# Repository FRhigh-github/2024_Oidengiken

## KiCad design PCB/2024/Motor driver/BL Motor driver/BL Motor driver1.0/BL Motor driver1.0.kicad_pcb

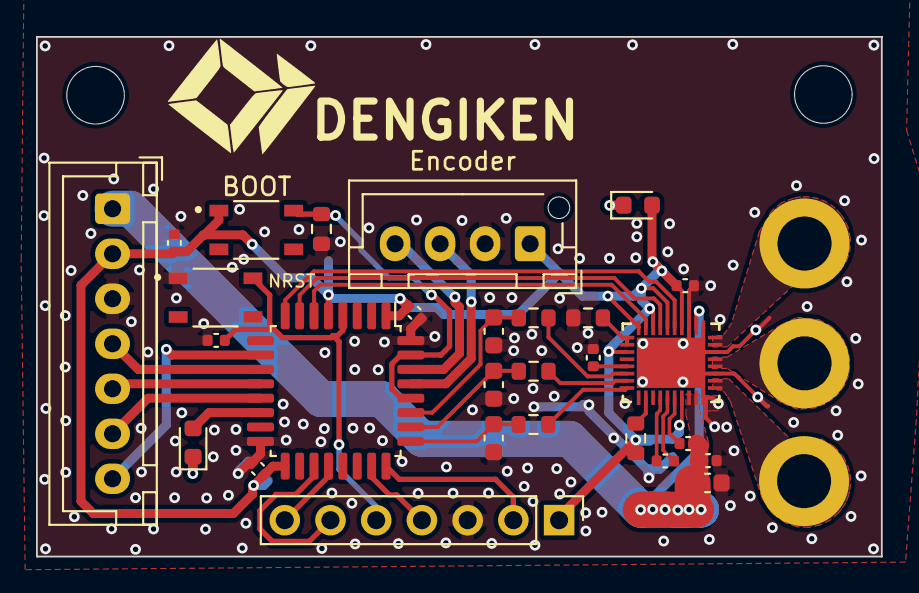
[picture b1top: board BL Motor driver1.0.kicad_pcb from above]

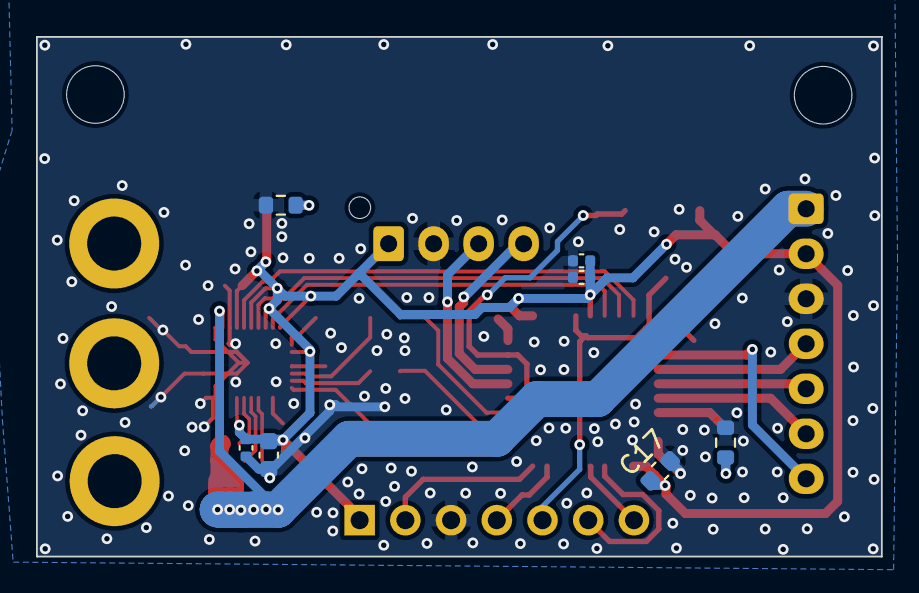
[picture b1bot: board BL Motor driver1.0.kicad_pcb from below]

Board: 2 copper layers, 46.9 x 28.9 mm, 38 parts (7 on the bottom side), 36 nets.

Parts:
BOOT: BOOT; SW_SKRPABE010
C1, C3, C6, C10, C12, C14, C16, C18: 0.1u; C_0402_1005Metric
C2, C4: 10u; C_0603_1608Metric
C5, C15: 1u; C_0402_1005Metric
C7, C8, C9: 22p; C_0603_1608Metric
C11: 2.2u; C_0402_1005Metric
C13: 0.01u; C_0402_1005Metric
C17: 4.7uf; C_0603_1608Metric
D1: UI_LED; LED_0603_1608Metric
D2: 3.3V_LED; LED_0603_1608Metric
Encoder: Encoder; JST_XH_B4B-XH-AM_1x04_P2.50mm_Vertical
J1: U; BLDC
J3: Main; JST_XH_B7B-XH-A_1x07_P2.50mm_Vertical
J4: V; BLDC
J6: PC; PinHeader_1x07_P2.54mm_Vertical
NRST: NRST; SW_SKRPABE010
R1, R2, R3: 330; R_0603_1608Metric
R4: 47k; R_0603_1608Metric
R5: 5.1k; R_0603_1608Metric
R6, R7, R8: 10k; R_0603_1608Metric
U1: DRV8317HREER
U2: STM32F303K8Tx; LQFP-32_7x7mm_P0.8mm
W: W; BLDC

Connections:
AGND: C1.2, C2.2, C3.2, C4.2, C7.2, C8.2, C9.2, C10.2, C11.2, C12.2, C13.2, C14.2, C15.2, C16.2, C17.2, C18.2, Encoder.2, J3.3, J6.3, NRST.1, R4.2, R6.2, R7.2, R8.2, U1.10 (PGND), U1.13 (PGND), U1.16 (PGND), U1.19 (PGND), U1.21 (AGND), U1.37 (EPAD), U2.16 (VSS), U2.32 (VSS)
AVDD: BOOT.1, C1.1, C2.1, C11.1, C12.1, C13.1, C14.1, C15.1, C16.1, C17.1, D2.2 (A), Encoder.1, J3.2, J6.1, R5.1, U1.7 (VIN_AVDD), U1.22 (AVDD), U1.24 (INLA), U1.26 (INLB), U1.28 (INLC), U1.31 (MODE), U2.1 (VDD), U2.5 (VDDA), U2.17 (VDD)
BOOT: BOOT.2, R6.1, U2.28 (PB5), U2.31 (BOOT0)
CP: C5.2, U1.6 (CP)
CPH: C6.1, U1.5 (CPH)
CPL: C6.2, U1.4 (CPL)
CSAREF: C10.1, U1.33 (CSAREF)
GAIN: R4.1, U1.29 (GAIN), U1.30 (SLEW)
I2C_SCL: Encoder.3, U2.29 (PB6)
I2C_SDA: Encoder.4, U2.30 (PB7)
NRST: C18.1, J6.5, NRST.2, U2.4 (NRST)
unnamed: D1.1 (K), R7.1
unnamed: D2.1 (K), R8.1
PWMU: U1.23 (INHA), U2.8 (PA2)
PWMV: U1.25 (INHB), U2.7 (PA1)
PWMW: U1.27 (INHC), U2.6 (PA0)
SOA: R1.2, U1.36 (SOA)
SOB: R2.2, U1.35 (SOB)
SOC: R3.2, U1.34 (SOC)
SOU: C7.1, R1.1, U2.25 (PA15)
SOV: C8.1, R2.1, U2.26 (PB3)
SOW: C9.1, R3.1, U2.27 (PB4)
SPI_CS: J3.7, U2.10 (PA4)
SPI_MISO: J3.5, U2.12 (PA6)
SPI_MOSI: J3.6, U2.13 (PA7)
SPI_SCK: J3.4, U2.11 (PA5)
SWCLK: J6.2, U2.24 (PA14)
SWDIO: J6.4, U2.23 (PA13)
U: J1.1, U1.11 (OUTA), U1.12 (OUTA)
UI_LED: D1.2 (A), U2.14 (PB0)
USART1_RX: J6.7, U2.20 (PA10)
USART1_TX: J6.6, U2.19 (PA9)
V: J4.1, U1.14 (OUTB), U1.15 (OUTB)
VM: C3.1, C4.1, C5.1, J3.1, U1.8 (VM), U1.9 (VM), U1.20 (VM)
W: U1.17 (OUTC), U1.18 (OUTC), W.1
nFAULT: R5.2, U1.2 (NFAULT)

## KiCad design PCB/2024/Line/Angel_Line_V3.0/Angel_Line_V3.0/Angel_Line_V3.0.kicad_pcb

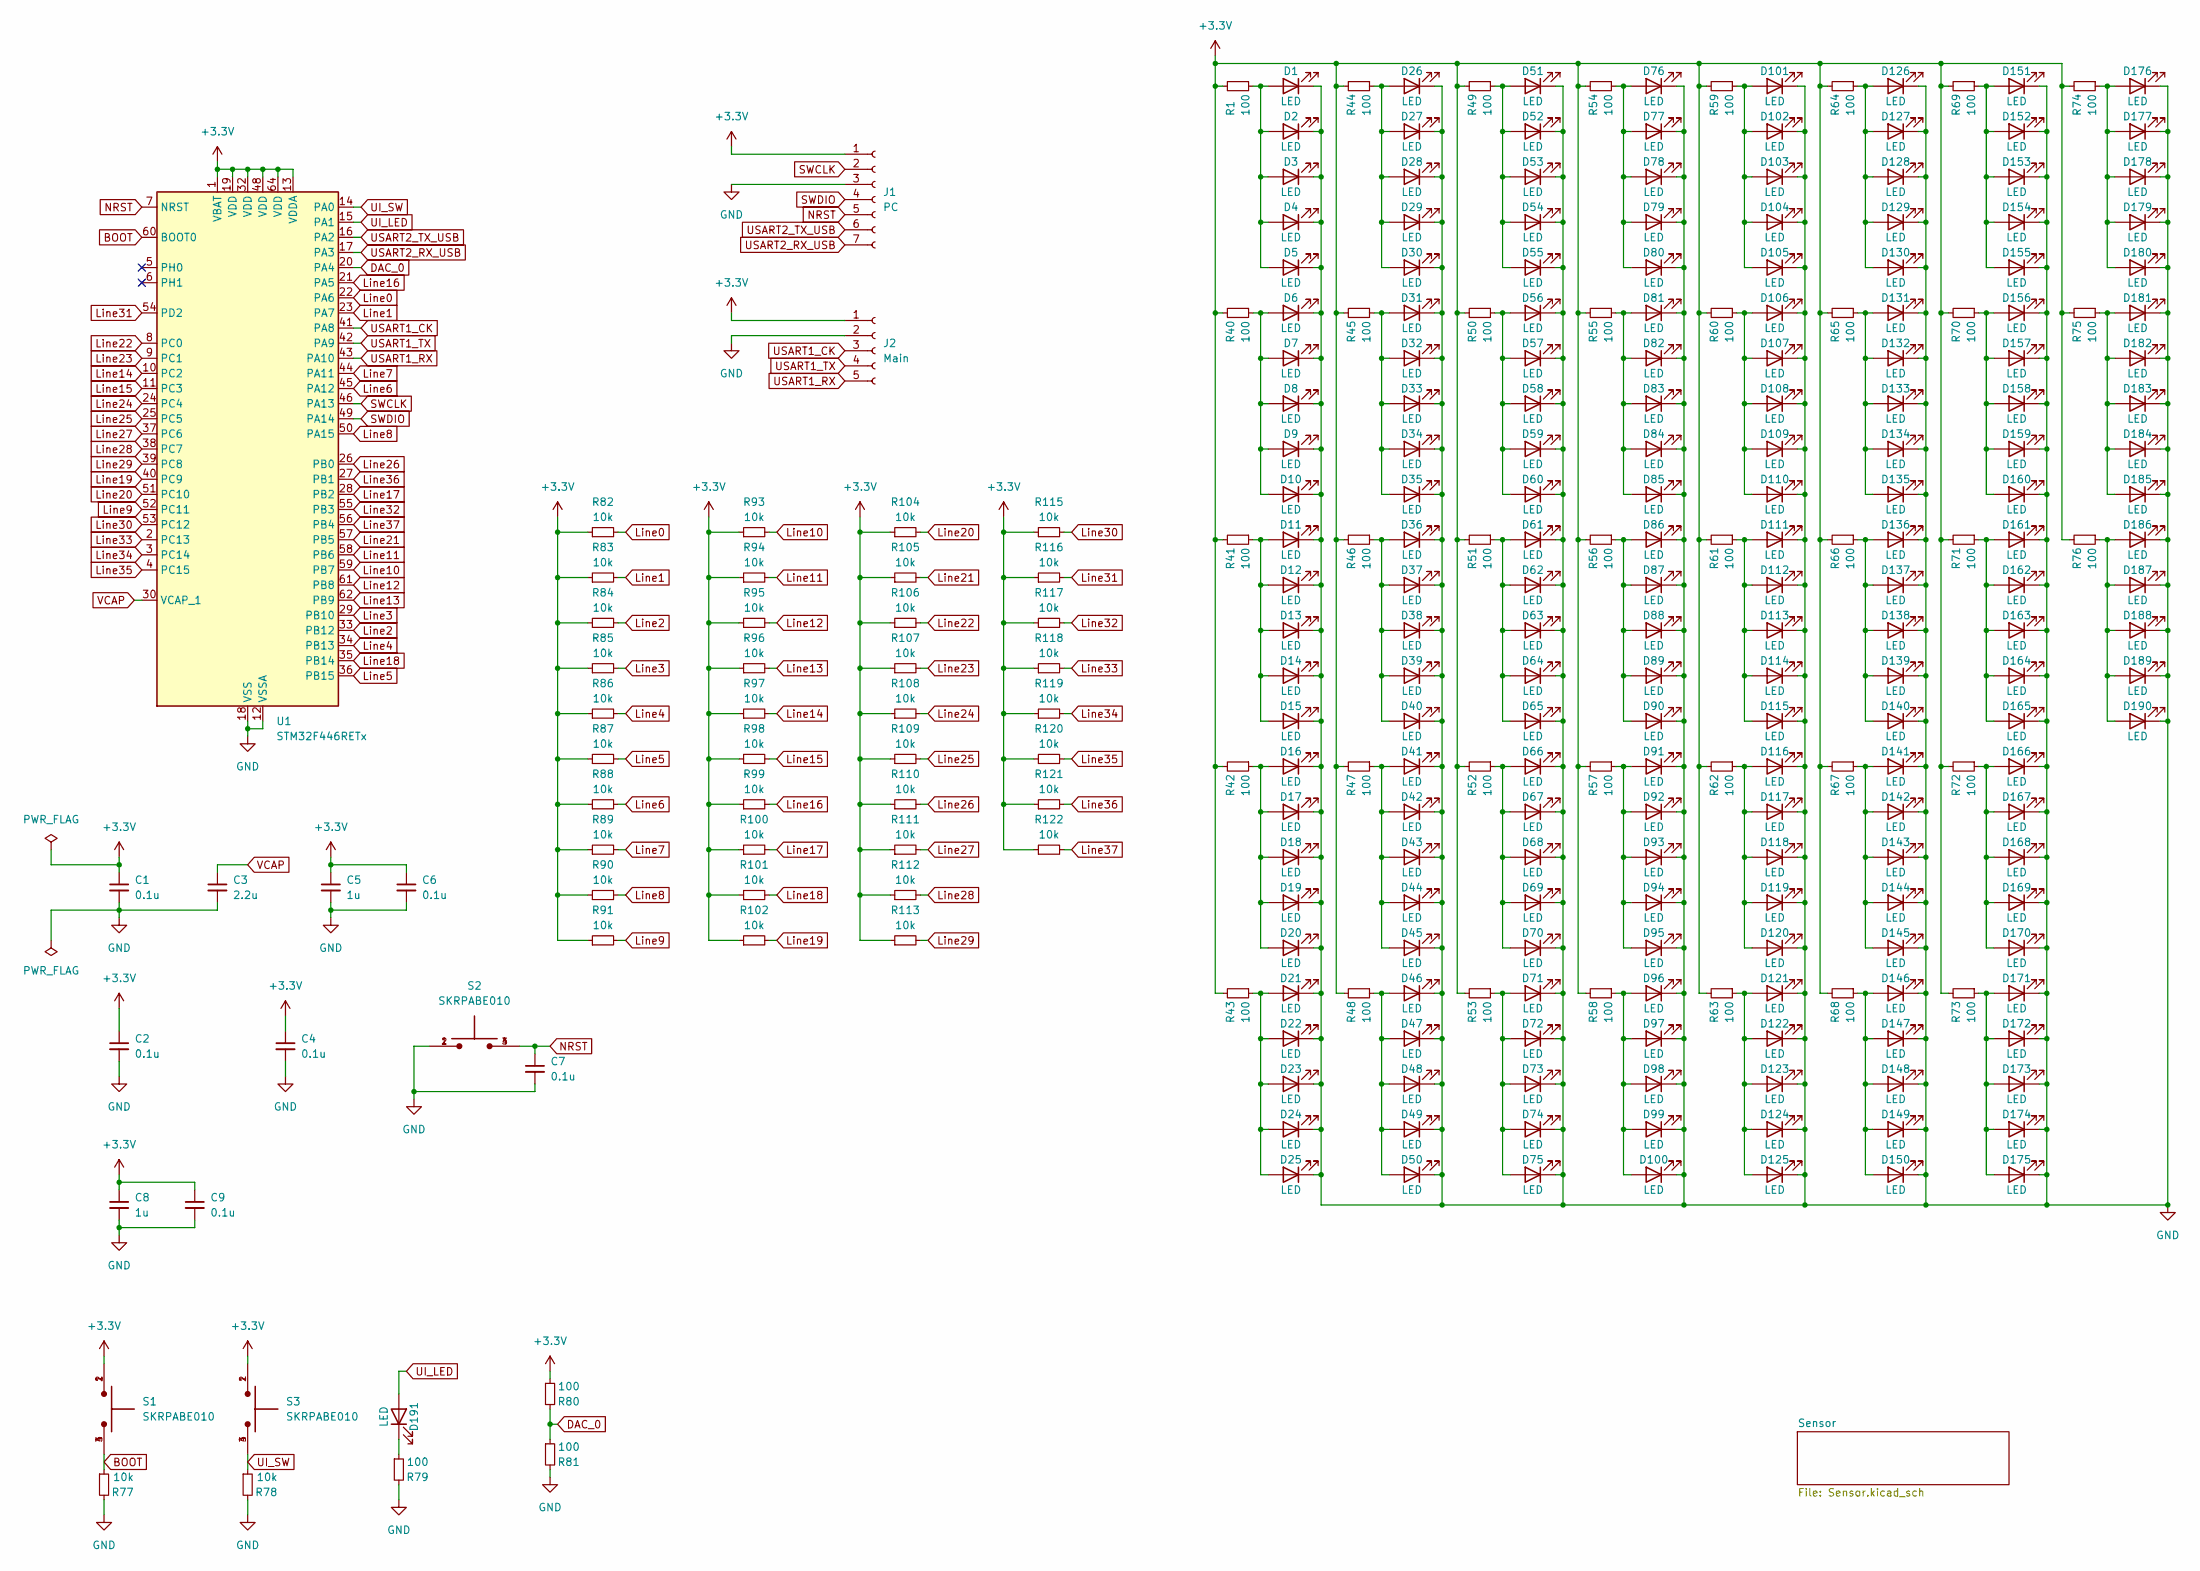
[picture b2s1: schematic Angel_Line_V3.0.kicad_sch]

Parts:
C1, C2, C4, C6, C7, C9: 0.1u; C_0402_1005Metric
C3: 2.2u; C_0603_1608Metric
C5, C8: 1u; C_0402_1005Metric
D1, D2, D3, D4, D5, D6, D7, D8, D9, D10, D11, D12, D13, D14, D15, D16, D17, D18, D19, D20, D21, D22, D23, D24, D25, D26, D27, D28, D29, D30, D31, D32, D33, D34, D35, D36, D37, D38, D39, D40, D41, D42, D43, D44, D45, D46, D47, D48, D49, D50, D51, D52, D53, D54, D55, D56, D57, D58, D59, D60, D61, D62, D63, D64, D65, D66, D67, D68, D69, D70, D71, D72, D73, D74, D75, D76, D77, D78, D79, D80, D81, D82, D83, D84, D85, D86, D87, D88, D89, D90, D91, D92, D93, D94, D95, D96, D97, D98, D99, D100, D101, D102, D103, D104, D105, D106, D107, D108, D109, D110, D111, D112, D113, D114, D115, D116, D117, D118, D119, D120, D121, D122, D123, D124, D125, D126, D127, D128, D129, D130, D131, D132, D133, D134, D135, D136, D137, D138, D139, D140, D141, D142, D143, D144, D145, D146, D147, D148, D149, D150, D151, D152, D153, D154, D155, D156, D157, D158, D159, D160, D161, D162, D163, D164, D165, D166, D167, D168, D169, D170, D171, D172, D173, D174, D175, D176, D177, D178, D179, D180, D181, D182, D183, D184, D185, D186, D187, D188, D189, D190, D191: LED; LED_0603_1608Metric
J1: PC; JST_XH_B7B-XH-A_1x07_P2.50mm_Vertical
J2: Main; JST_XH_B5B-XH-A_1x05_P2.50mm_Vertical
R1, R40, R41, R42, R43, R44, R45, R46, R47, R48, R49, R50, R51, R52, R53, R54, R55, R56, R57, R58, R59, R60, R61, R62, R63, R64, R65, R66, R67, R68, R69, R70, R71, R72, R73, R74, R75, R76, R79, R80, R81: 100; R_0603_1608Metric
R77, R78, R82, R83, R84, R85, R86, R87, R88, R89, R90, R91, R93, R94, R95, R96, R97, R98, R99, R100, R101, R102, R104, R105, R106, R107, R108, R109, R110, R111, R112, R113, R115, R116, R117, R118, R119, R120, R121, R122: 10k; R_0603_1608Metric
S1, S2, S3: SKRPABE010; SW_SKRPABE010
U1: STM32F446RETx; LQFP-64_10x10mm_P0.5mm

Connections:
+3.3V: C1.1, C2.1, C4.1, C5.1, C6.1, C8.1, C9.1, J1.1, J2.1, R1.2, R40.2, R41.2, R42.2, R43.2, R44.2, R45.2, R46.2, R47.2, R48.2, R49.2, R50.2, R51.2, R52.2, R53.2, R54.2, R55.2, R56.2, R57.2, R58.2, R59.2, R60.2, R61.2, R62.2, R63.2, R64.2, R65.2, R66.2, R67.2, R68.2, R69.2, R70.2, R71.2, R72.2, R73.2, R74.2, R75.2, R76.2, R80.1, R82.1, R83.1, R84.1, R85.1, R86.1, R87.1, R88.1, R89.1, R90.1, R91.1, R93.1, R94.1, R95.1, R96.1, R97.1, R98.1, R99.1, R100.1, R101.1, R102.1, R104.1, R105.1, R106.1, R107.1, R108.1, R109.1, R110.1, R111.1, R112.1, R113.1, R115.1, R116.1, R117.1, R118.1, R119.1, R120.1, R121.1, R122.1, S1.1, S1.2, S3.1, S3.2, U1.1 (VBAT), U1.13 (VDDA), U1.19 (VDD), U1.32 (VDD), U1.48 (VDD), U1.64 (VDD); also elsewhere on the board
BOOT: R77.1, S1.3, S1.4, U1.60 (BOOT0)
DAC_0: R80.2, R81.1, U1.20 (PA4); also elsewhere on the board
GND: C1.2, C2.2, C3.2, C4.2, C5.2, C6.2, C7.2, C8.2, C9.2, D1.1 (K), D2.1 (K), D3.1 (K), D4.1 (K), D5.1 (K), D6.1 (K), D7.1 (K), D8.1 (K), D9.1 (K), D10.1 (K), D11.1 (K), D12.1 (K), D13.1 (K), D14.1 (K), D15.1 (K), D16.1 (K), D17.1 (K), D18.1 (K), D19.1 (K), D20.1 (K), D21.1 (K), D22.1 (K), D23.1 (K), D24.1 (K), D25.1 (K), D26.1 (K), D27.1 (K), D28.1 (K), D29.1 (K), D30.1 (K), D31.1 (K), D32.1 (K), D33.1 (K), D34.1 (K), D35.1 (K), D36.1 (K), D37.1 (K), D38.1 (K), D39.1 (K), D40.1 (K), D41.1 (K), D42.1 (K), D43.1 (K), D44.1 (K), D45.1 (K), D46.1 (K), D47.1 (K), D48.1 (K), D49.1 (K), D50.1 (K), D51.1 (K), D52.1 (K), D53.1 (K), D54.1 (K), D55.1 (K), D56.1 (K), D57.1 (K), D58.1 (K), D59.1 (K), D60.1 (K), D61.1 (K), D62.1 (K), D63.1 (K), D64.1 (K), D65.1 (K), D66.1 (K), D67.1 (K), D68.1 (K), D69.1 (K), D70.1 (K), D71.1 (K), D72.1 (K), D73.1 (K), D74.1 (K), D75.1 (K), D76.1 (K), D77.1 (K), D78.1 (K), D79.1 (K), D80.1 (K), D81.1 (K), D82.1 (K), D83.1 (K), D84.1 (K), D85.1 (K), D86.1 (K), D87.1 (K), D88.1 (K), D89.1 (K), D90.1 (K), D91.1 (K), D92.1 (K), D93.1 (K), D94.1 (K), D95.1 (K), D96.1 (K), D97.1 (K), D98.1 (K), D99.1 (K), D100.1 (K), D101.1 (K), D102.1 (K), D103.1 (K), D104.1 (K), D105.1 (K), D106.1 (K), D107.1 (K), D108.1 (K), D109.1 (K), D110.1 (K), D111.1 (K), D112.1 (K), D113.1 (K), D114.1 (K), D115.1 (K), D116.1 (K), D117.1 (K), D118.1 (K), D119.1 (K), D120.1 (K), D121.1 (K), D122.1 (K), D123.1 (K), D124.1 (K), D125.1 (K), D126.1 (K), D127.1 (K), D128.1 (K), D129.1 (K), D130.1 (K), D131.1 (K), D132.1 (K), D133.1 (K), D134.1 (K), D135.1 (K), D136.1 (K), D137.1 (K), D138.1 (K), D139.1 (K), D140.1 (K), D141.1 (K), D142.1 (K), D143.1 (K), D144.1 (K), D145.1 (K), D146.1 (K), D147.1 (K), D148.1 (K), D149.1 (K), D150.1 (K), D151.1 (K), D152.1 (K), D153.1 (K), D154.1 (K), D155.1 (K), D156.1 (K), D157.1 (K), D158.1 (K), D159.1 (K), D160.1 (K), D161.1 (K), D162.1 (K), D163.1 (K), D164.1 (K), D165.1 (K), D166.1 (K), D167.1 (K), D168.1 (K), D169.1 (K), D170.1 (K), D171.1 (K), D172.1 (K), D173.1 (K), D174.1 (K), D175.1 (K), D176.1 (K), D177.1 (K), D178.1 (K), D179.1 (K), D180.1 (K), D181.1 (K), D182.1 (K), D183.1 (K), D184.1 (K), D185.1 (K), D186.1 (K), D187.1 (K), D188.1 (K), D189.1 (K), D190.1 (K), J1.3, J2.2, R77.2, R78.2, R79.2, R81.2, S2.1, S2.2, U1.12 (VSSA), U1.18 (VSS), U1.31 (VSS), U1.47 (VSS), U1.63 (VSS); also elsewhere on the board
Line0: R82.2, U1.22 (PA6); also elsewhere on the board
Line1: R83.2, U1.23 (PA7); also elsewhere on the board
Line2: R84.2, U1.33 (PB12); also elsewhere on the board
Line3: R85.2, U1.29 (PB10); also elsewhere on the board
Line4: R86.2, U1.34 (PB13); also elsewhere on the board
Line5: R87.2, U1.36 (PB15); also elsewhere on the board
Line6: R88.2, U1.45 (PA12); also elsewhere on the board
Line7: R89.2, U1.44 (PA11); also elsewhere on the board
Line8: R90.2, U1.50 (PA15); also elsewhere on the board
Line9: R91.2, U1.52 (PC11); also elsewhere on the board
Line10: R93.2, U1.59 (PB7); also elsewhere on the board
Line11: R94.2, U1.58 (PB6); also elsewhere on the board
Line12: R95.2, U1.61 (PB8); also elsewhere on the board
Line13: R96.2, U1.62 (PB9); also elsewhere on the board
Line14: R97.2, U1.10 (PC2); also elsewhere on the board
Line15: R98.2, U1.11 (PC3); also elsewhere on the board
Line16: R99.2, U1.21 (PA5); also elsewhere on the board
Line17: R100.2, U1.28 (PB2); also elsewhere on the board
Line18: R101.2, U1.35 (PB14); also elsewhere on the board
Line19: R102.2, U1.40 (PC9); also elsewhere on the board
Line20: R104.2, U1.51 (PC10); also elsewhere on the board
Line21: R105.2, U1.57 (PB5); also elsewhere on the board
Line22: R106.2, U1.8 (PC0); also elsewhere on the board
Line23: R107.2, U1.9 (PC1); also elsewhere on the board
Line24: R108.2, U1.24 (PC4); also elsewhere on the board
Line25: R109.2, U1.25 (PC5); also elsewhere on the board
Line26: R110.2, U1.26 (PB0); also elsewhere on the board
Line27: R111.2, U1.37 (PC6); also elsewhere on the board
Line28: R112.2, U1.38 (PC7); also elsewhere on the board
Line29: R113.2, U1.39 (PC8); also elsewhere on the board
Line30: R115.2, U1.53 (PC12); also elsewhere on the board
Line31: R116.2, U1.54 (PD2); also elsewhere on the board
Line32: R117.2, U1.55 (PB3); also elsewhere on the board
Line33: R118.2, U1.2 (PC13); also elsewhere on the board
Line34: R119.2, U1.3 (PC14); also elsewhere on the board
Line35: R120.2, U1.4 (PC15); also elsewhere on the board
Line36: R121.2, U1.27 (PB1); also elsewhere on the board
Line37: R122.2, U1.56 (PB4); also elsewhere on the board
NRST: C7.1, J1.5, S2.3, S2.4, U1.7 (NRST)
unnamed: D1.2 (A), D2.2 (A), D3.2 (A), D4.2 (A), D5.2 (A), R1.1
unnamed: D6.2 (A), D7.2 (A), D8.2 (A), D9.2 (A), D10.2 (A), R40.1
unnamed: D11.2 (A), D12.2 (A), D13.2 (A), D14.2 (A), D15.2 (A), R41.1
unnamed: D16.2 (A), D17.2 (A), D18.2 (A), D19.2 (A), D20.2 (A), R42.1
unnamed: D21.2 (A), D22.2 (A), D23.2 (A), D24.2 (A), D25.2 (A), R43.1
unnamed: D26.2 (A), D27.2 (A), D28.2 (A), D29.2 (A), D30.2 (A), R44.1
unnamed: D31.2 (A), D32.2 (A), D33.2 (A), D34.2 (A), D35.2 (A), R45.1
unnamed: D36.2 (A), D37.2 (A), D38.2 (A), D39.2 (A), D40.2 (A), R46.1
unnamed: D41.2 (A), D42.2 (A), D43.2 (A), D44.2 (A), D45.2 (A), R47.1
unnamed: D46.2 (A), D47.2 (A), D48.2 (A), D49.2 (A), D50.2 (A), R48.1
unnamed: D51.2 (A), D52.2 (A), D53.2 (A), D54.2 (A), D55.2 (A), R49.1
unnamed: D56.2 (A), D57.2 (A), D58.2 (A), D59.2 (A), D60.2 (A), R50.1
unnamed: D61.2 (A), D62.2 (A), D63.2 (A), D64.2 (A), D65.2 (A), R51.1
unnamed: D66.2 (A), D67.2 (A), D68.2 (A), D69.2 (A), D70.2 (A), R52.1
unnamed: D71.2 (A), D72.2 (A), D73.2 (A), D74.2 (A), D75.2 (A), R53.1
unnamed: D76.2 (A), D77.2 (A), D78.2 (A), D79.2 (A), D80.2 (A), R54.1
unnamed: D81.2 (A), D82.2 (A), D83.2 (A), D84.2 (A), D85.2 (A), R55.1
unnamed: D86.2 (A), D87.2 (A), D88.2 (A), D89.2 (A), D90.2 (A), R56.1
unnamed: D91.2 (A), D92.2 (A), D93.2 (A), D94.2 (A), D95.2 (A), R57.1
unnamed: D96.2 (A), D97.2 (A), D98.2 (A), D99.2 (A), D100.2 (A), R58.1
unnamed: D101.2 (A), D102.2 (A), D103.2 (A), D104.2 (A), D105.2 (A), R59.1
unnamed: D106.2 (A), D107.2 (A), D108.2 (A), D109.2 (A), D110.2 (A), R60.1
unnamed: D111.2 (A), D112.2 (A), D113.2 (A), D114.2 (A), D115.2 (A), R61.1
unnamed: D116.2 (A), D117.2 (A), D118.2 (A), D119.2 (A), D120.2 (A), R62.1
unnamed: D121.2 (A), D122.2 (A), D123.2 (A), D124.2 (A), D125.2 (A), R63.1
unnamed: D126.2 (A), D127.2 (A), D128.2 (A), D129.2 (A), D130.2 (A), R64.1
unnamed: D131.2 (A), D132.2 (A), D133.2 (A), D134.2 (A), D135.2 (A), R65.1
unnamed: D136.2 (A), D137.2 (A), D138.2 (A), D139.2 (A), D140.2 (A), R66.1
unnamed: D141.2 (A), D142.2 (A), D143.2 (A), D144.2 (A), D145.2 (A), R67.1
unnamed: D146.2 (A), D147.2 (A), D148.2 (A), D149.2 (A), D150.2 (A), R68.1
unnamed: D151.2 (A), D152.2 (A), D153.2 (A), D154.2 (A), D155.2 (A), R69.1
unnamed: D156.2 (A), D157.2 (A), D158.2 (A), D159.2 (A), D160.2 (A), R70.1
unnamed: D161.2 (A), D162.2 (A), D163.2 (A), D164.2 (A), D165.2 (A), R71.1
unnamed: D166.2 (A), D167.2 (A), D168.2 (A), D169.2 (A), D170.2 (A), R72.1
unnamed: D171.2 (A), D172.2 (A), D173.2 (A), D174.2 (A), D175.2 (A), R73.1
unnamed: D176.2 (A), D177.2 (A), D178.2 (A), D179.2 (A), D180.2 (A), R74.1
unnamed: D181.2 (A), D182.2 (A), D183.2 (A), D184.2 (A), D185.2 (A), R75.1
unnamed: D186.2 (A), D187.2 (A), D188.2 (A), D189.2 (A), D190.2 (A), R76.1
unnamed: D191.1 (K), R79.1
SWCLK: J1.2, U1.46 (PA13)
SWDIO: J1.4, U1.49 (PA14)
UI_LED: D191.2 (A), U1.15 (PA1)
UI_SW: R78.1, S3.3, S3.4, U1.14 (PA0)
USART1_CK: J2.3, U1.41 (PA8)
USART1_RX: J2.5, U1.43 (PA10)
USART1_TX: J2.4, U1.42 (PA9)
USART2_RX_USB: J1.7, U1.17 (PA3)
USART2_TX_USB: J1.6, U1.16 (PA2)
VCAP: C3.1, U1.30 (VCAP_1)

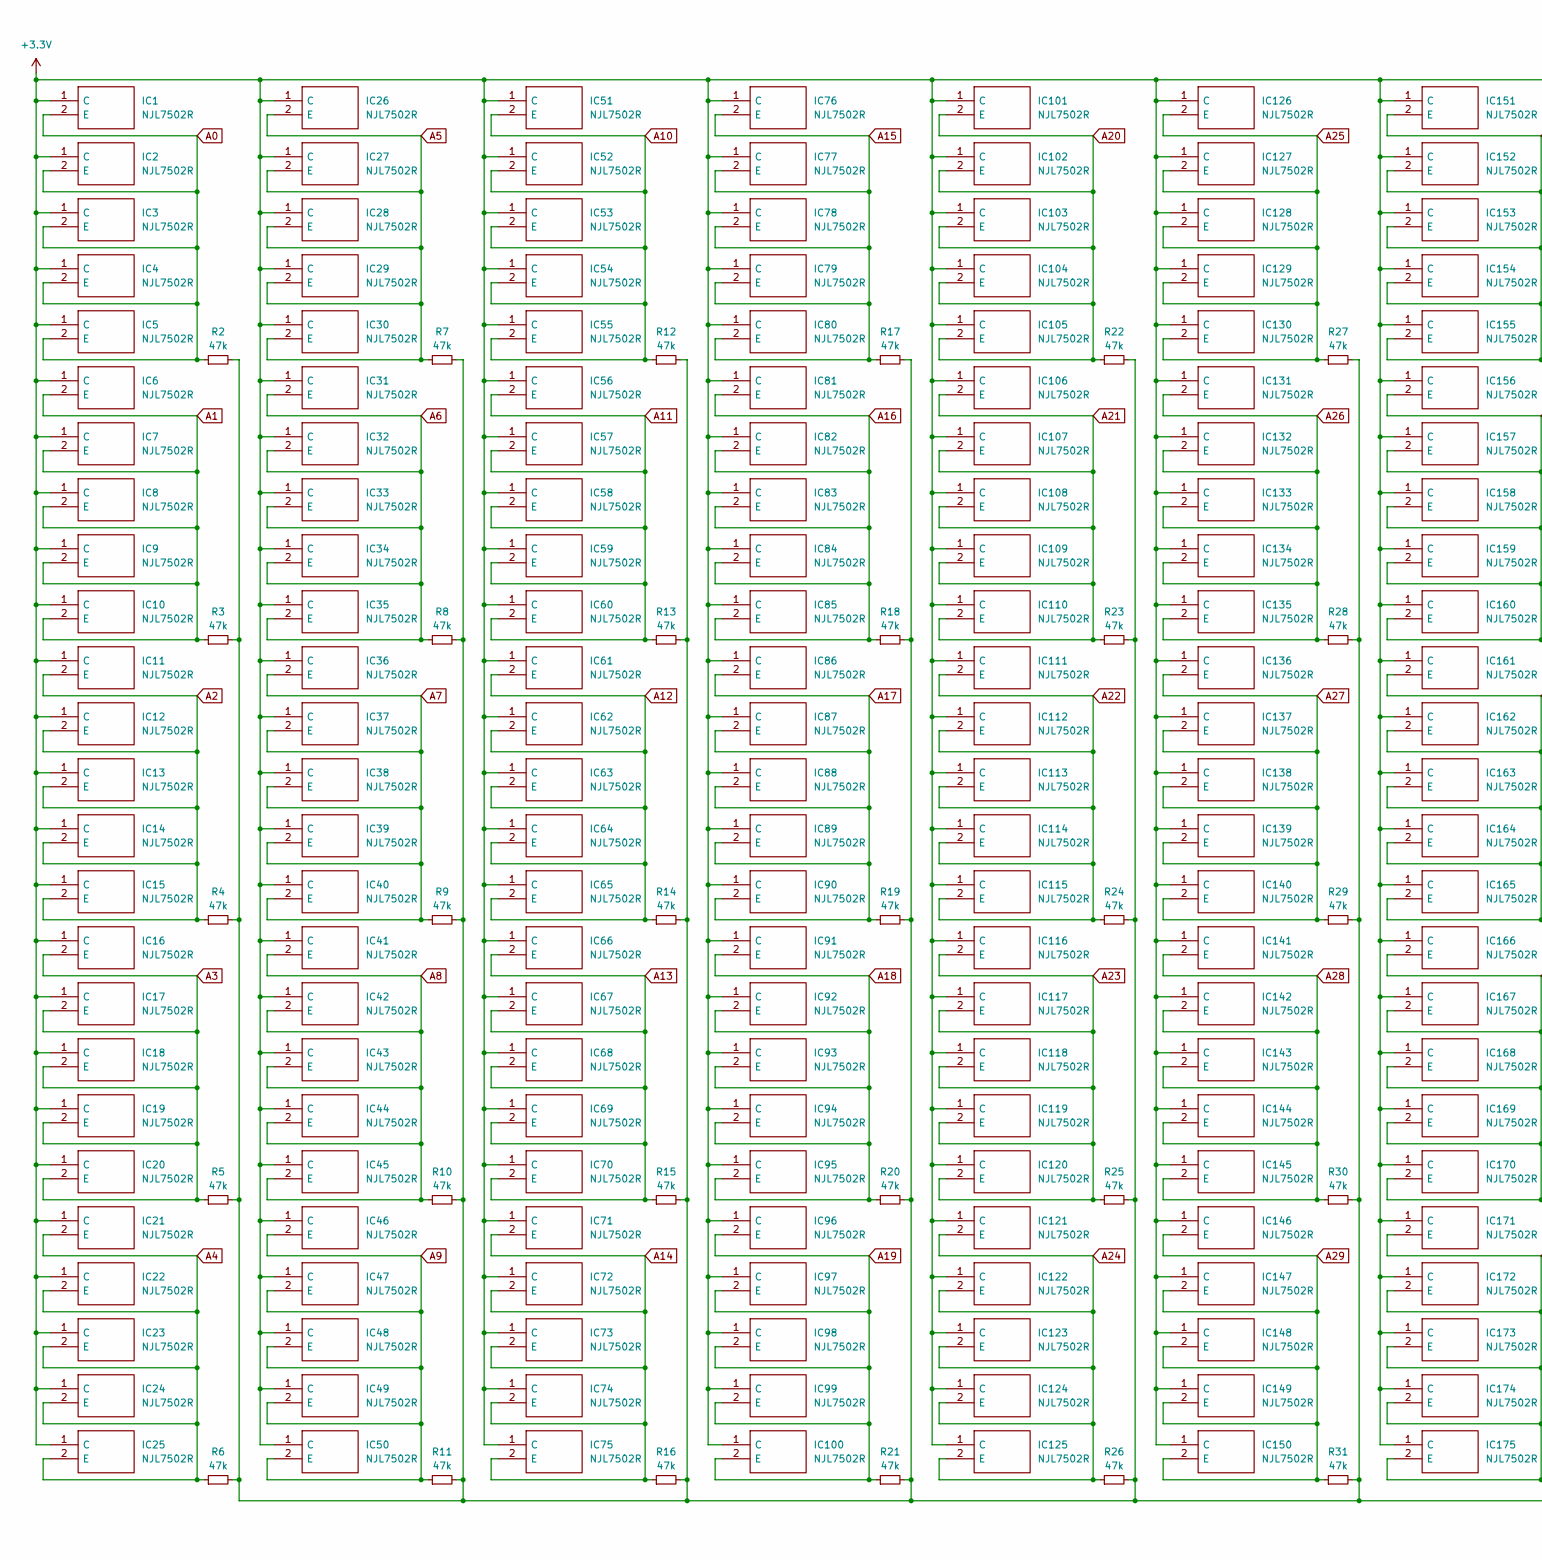
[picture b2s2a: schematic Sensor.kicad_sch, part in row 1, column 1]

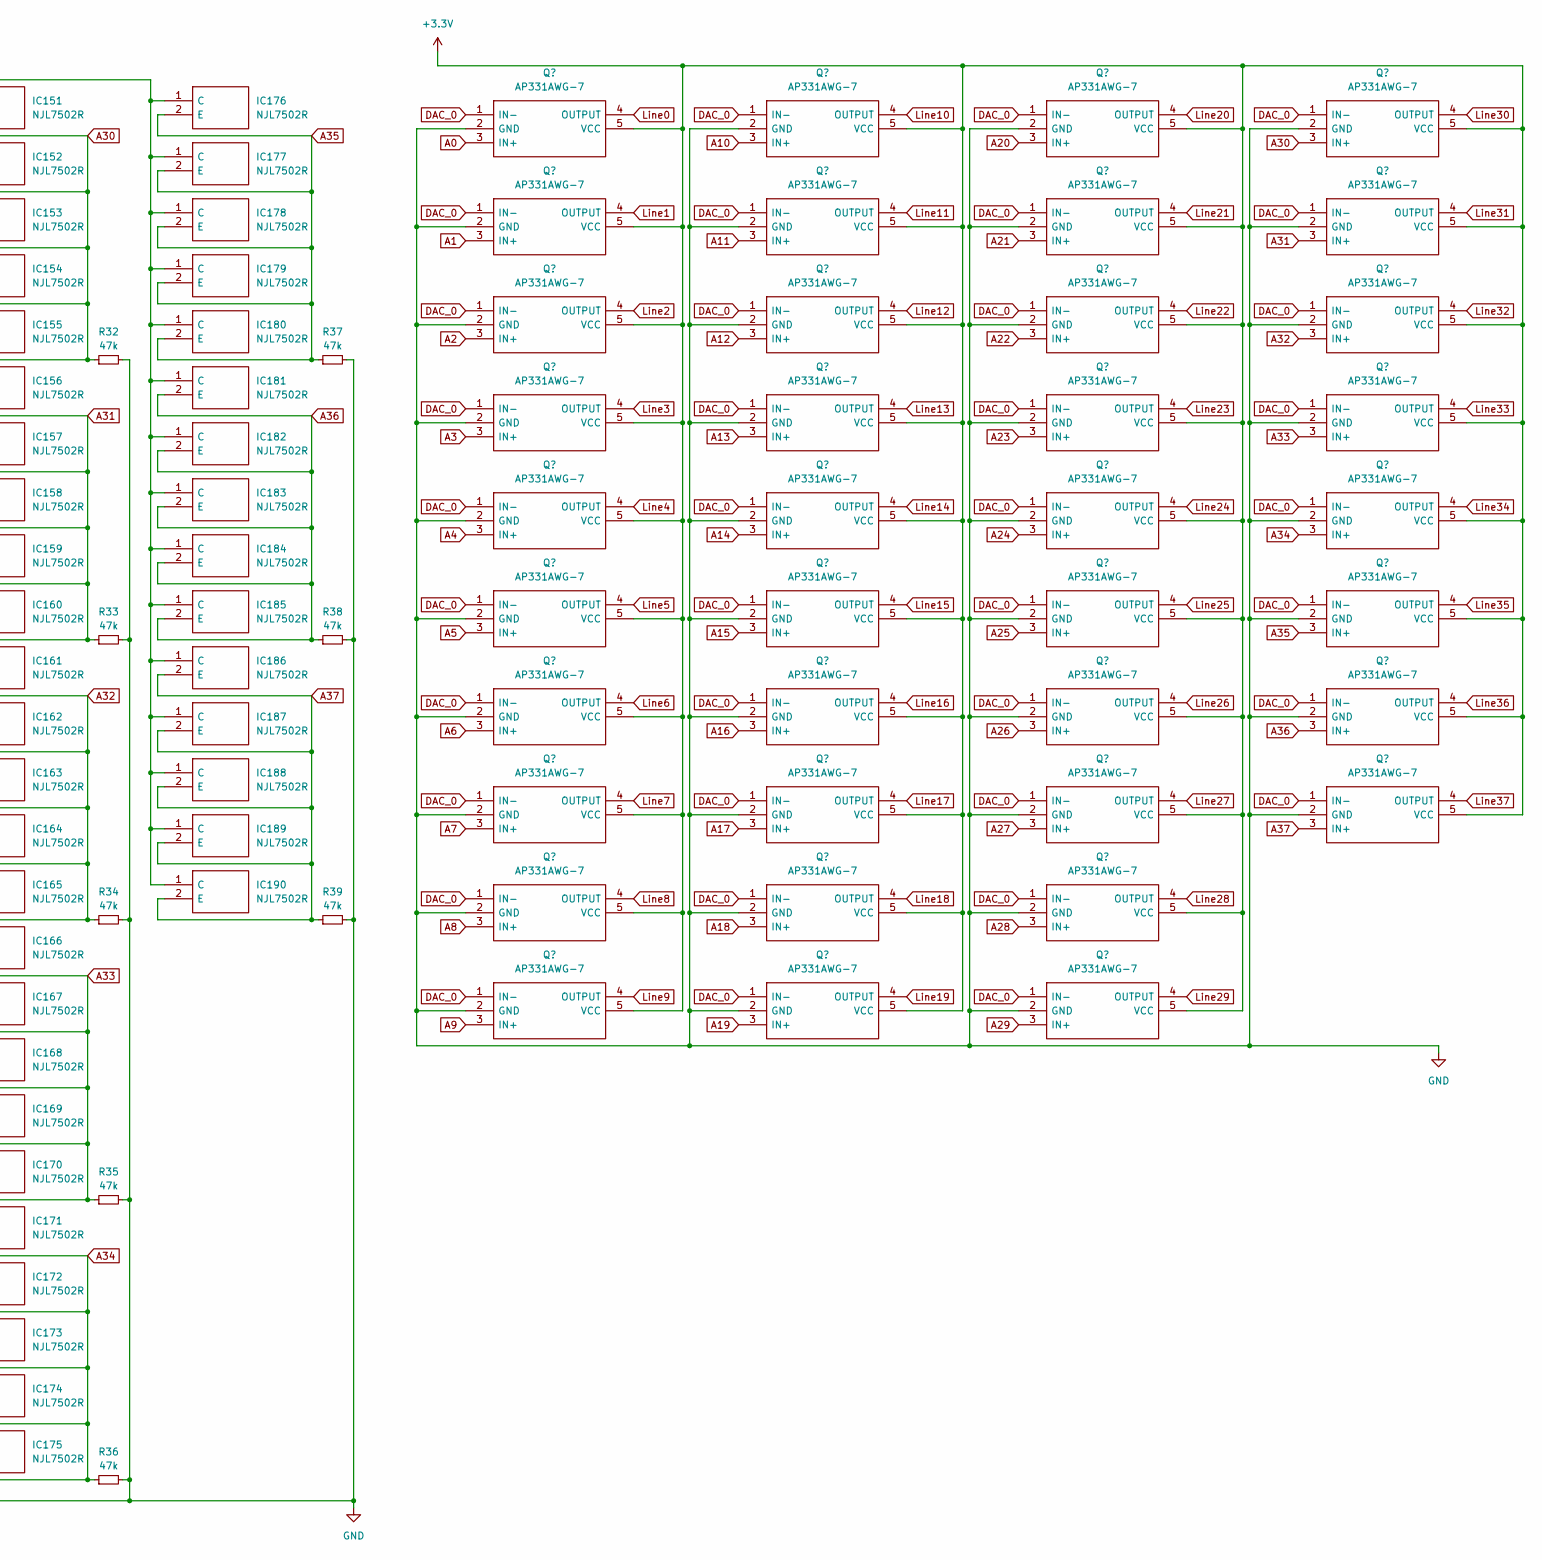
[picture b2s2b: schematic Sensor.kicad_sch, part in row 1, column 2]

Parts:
IC1, IC2, IC3, IC4, IC5, IC6, IC7, IC8, IC9, IC10, IC11, IC12, IC13, IC14, IC15, IC16, IC17, IC18, IC19, IC20, IC21, IC22, IC23, IC24, IC25, IC26, IC27, IC28, IC29, IC30, IC31, IC32, IC33, IC34, IC35, IC36, IC37, IC38, IC39, IC40, IC41, IC42, IC43, IC44, IC45, IC46, IC47, IC48, IC49, IC50, IC51, IC52, IC53, IC54, IC55, IC56, IC57, IC58, IC59, IC60, IC61, IC62, IC63, IC64, IC65, IC66, IC67, IC68, IC69, IC70, IC71, IC72, IC73, IC74, IC75, IC76, IC77, IC78, IC79, IC80, IC81, IC82, IC83, IC84, IC85, IC86, IC87, IC88, IC89, IC90, IC91, IC92, IC93, IC94, IC95, IC96, IC97, IC98, IC99, IC100, IC101, IC102, IC103, IC104, IC105, IC106, IC107, IC108, IC109, IC110, IC111, IC112, IC113, IC114, IC115, IC116, IC117, IC118, IC119, IC120, IC121, IC122, IC123, IC124, IC125, IC126, IC127, IC128, IC129, IC130, IC131, IC132, IC133, IC134, IC135, IC136, IC137, IC138, IC139, IC140, IC141, IC142, IC143, IC144, IC145, IC146, IC147, IC148, IC149, IC150, IC151, IC152, IC153, IC154, IC155, IC156, IC157, IC158, IC159, IC160, IC161, IC162, IC163, IC164, IC165, IC166, IC167, IC168, IC169, IC170, IC171, IC172, IC173, IC174, IC175, IC176, IC177, IC178, IC179, IC180, IC181, IC182, IC183, IC184, IC185, IC186, IC187, IC188, IC189, IC190: NJL7502R; Manufacturer_Part_Number NJL7502R
Q1, Q2, Q3, Q4, Q5, Q6, Q7, Q8, Q9, Q10, Q11, Q12, Q13, Q14, Q15, Q16, Q17, Q18, Q19, Q20, Q21, Q22, Q23, Q24, Q25, Q26, Q27, Q28, Q29, Q30, Q31, Q32, Q33, Q34, Q35, Q36, Q37, Q38: AP331AWG-7; SOT95P285X130-5N; Mouser Part Number 621-AP331AWG-7
R2, R3, R4, R5, R6, R7, R8, R9, R10, R11, R12, R13, R14, R15, R16, R17, R18, R19, R20, R21, R22, R23, R24, R25, R26, R27, R28, R29, R30, R31, R32, R33, R34, R35, R36, R37, R38, R39: 47k; R_0603_1608Metric

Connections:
+3.3V: IC1.1 (C), IC2.1 (C), IC3.1 (C), IC4.1 (C), IC5.1 (C), IC6.1 (C), IC7.1 (C), IC8.1 (C), IC9.1 (C), IC10.1 (C), IC11.1 (C), IC12.1 (C), IC13.1 (C), IC14.1 (C), IC15.1 (C), IC16.1 (C), IC17.1 (C), IC18.1 (C), IC19.1 (C), IC20.1 (C), IC21.1 (C), IC22.1 (C), IC23.1 (C), IC24.1 (C), IC25.1 (C), IC26.1 (C), IC27.1 (C), IC28.1 (C), IC29.1 (C), IC30.1 (C), IC31.1 (C), IC32.1 (C), IC33.1 (C), IC34.1 (C), IC35.1 (C), IC36.1 (C), IC37.1 (C), IC38.1 (C), IC39.1 (C), IC40.1 (C), IC41.1 (C), IC42.1 (C), IC43.1 (C), IC44.1 (C), IC45.1 (C), IC46.1 (C), IC47.1 (C), IC48.1 (C), IC49.1 (C), IC50.1 (C), IC51.1 (C), IC52.1 (C), IC53.1 (C), IC54.1 (C), IC55.1 (C), IC56.1 (C), IC57.1 (C), IC58.1 (C), IC59.1 (C), IC60.1 (C), IC61.1 (C), IC62.1 (C), IC63.1 (C), IC64.1 (C), IC65.1 (C), IC66.1 (C), IC67.1 (C), IC68.1 (C), IC69.1 (C), IC70.1 (C), IC71.1 (C), IC72.1 (C), IC73.1 (C), IC74.1 (C), IC75.1 (C), IC76.1 (C), IC77.1 (C), IC78.1 (C), IC79.1 (C), IC80.1 (C), IC81.1 (C), IC82.1 (C), IC83.1 (C), IC84.1 (C), IC85.1 (C), IC86.1 (C), IC87.1 (C), IC88.1 (C), IC89.1 (C), IC90.1 (C), IC91.1 (C), IC92.1 (C), IC93.1 (C), IC94.1 (C), IC95.1 (C), IC96.1 (C), IC97.1 (C), IC98.1 (C), IC99.1 (C), IC100.1 (C), IC101.1 (C), IC102.1 (C), IC103.1 (C), IC104.1 (C), IC105.1 (C), IC106.1 (C), IC107.1 (C), IC108.1 (C), IC109.1 (C), IC110.1 (C), IC111.1 (C), IC112.1 (C), IC113.1 (C), IC114.1 (C), IC115.1 (C), IC116.1 (C), IC117.1 (C), IC118.1 (C), IC119.1 (C), IC120.1 (C), IC121.1 (C), IC122.1 (C), IC123.1 (C), IC124.1 (C), IC125.1 (C), IC126.1 (C), IC127.1 (C), IC128.1 (C), IC129.1 (C), IC130.1 (C), IC131.1 (C), IC132.1 (C), IC133.1 (C), IC134.1 (C), IC135.1 (C), IC136.1 (C), IC137.1 (C), IC138.1 (C), IC139.1 (C), IC140.1 (C), IC141.1 (C), IC142.1 (C), IC143.1 (C), IC144.1 (C), IC145.1 (C), IC146.1 (C), IC147.1 (C), IC148.1 (C), IC149.1 (C), IC150.1 (C), IC151.1 (C), IC152.1 (C), IC153.1 (C), IC154.1 (C), IC155.1 (C), IC156.1 (C), IC157.1 (C), IC158.1 (C), IC159.1 (C), IC160.1 (C), IC161.1 (C), IC162.1 (C), IC163.1 (C), IC164.1 (C), IC165.1 (C), IC166.1 (C), IC167.1 (C), IC168.1 (C), IC169.1 (C), IC170.1 (C), IC171.1 (C), IC172.1 (C), IC173.1 (C), IC174.1 (C), IC175.1 (C), IC176.1 (C), IC177.1 (C), IC178.1 (C), IC179.1 (C), IC180.1 (C), IC181.1 (C), IC182.1 (C), IC183.1 (C), IC184.1 (C), IC185.1 (C), IC186.1 (C), IC187.1 (C), IC188.1 (C), IC189.1 (C), IC190.1 (C), Q1.5 (VCC), Q2.5 (VCC), Q3.5 (VCC), Q4.5 (VCC), Q5.5 (VCC), Q6.5 (VCC), Q7.5 (VCC), Q8.5 (VCC), Q9.5 (VCC), Q10.5 (VCC), Q11.5 (VCC), Q12.5 (VCC), Q13.5 (VCC), Q14.5 (VCC), Q15.5 (VCC), Q16.5 (VCC), Q17.5 (VCC), Q18.5 (VCC), Q19.5 (VCC), Q20.5 (VCC), Q21.5 (VCC), Q22.5 (VCC), Q23.5 (VCC), Q24.5 (VCC), Q25.5 (VCC), Q26.5 (VCC), Q27.5 (VCC), Q28.5 (VCC), Q29.5 (VCC), Q30.5 (VCC), Q31.5 (VCC), Q32.5 (VCC), Q33.5 (VCC), Q34.5 (VCC), Q35.5 (VCC), Q36.5 (VCC), Q37.5 (VCC), Q38.5 (VCC); also elsewhere on the board
A0: IC1.2 (E), IC2.2 (E), IC3.2 (E), IC4.2 (E), IC5.2 (E), Q1.3 (IN+), R2.1
A1: IC6.2 (E), IC7.2 (E), IC8.2 (E), IC9.2 (E), IC10.2 (E), Q2.3 (IN+), R3.1
A2: IC11.2 (E), IC12.2 (E), IC13.2 (E), IC14.2 (E), IC15.2 (E), Q3.3 (IN+), R4.1
A3: IC16.2 (E), IC17.2 (E), IC18.2 (E), IC19.2 (E), IC20.2 (E), Q4.3 (IN+), R5.1
A4: IC21.2 (E), IC22.2 (E), IC23.2 (E), IC24.2 (E), IC25.2 (E), Q5.3 (IN+), R6.1
A5: IC26.2 (E), IC27.2 (E), IC28.2 (E), IC29.2 (E), IC30.2 (E), Q6.3 (IN+), R7.1
A6: IC31.2 (E), IC32.2 (E), IC33.2 (E), IC34.2 (E), IC35.2 (E), Q7.3 (IN+), R8.1
A7: IC36.2 (E), IC37.2 (E), IC38.2 (E), IC39.2 (E), IC40.2 (E), Q8.3 (IN+), R9.1
A8: IC41.2 (E), IC42.2 (E), IC43.2 (E), IC44.2 (E), IC45.2 (E), Q9.3 (IN+), R10.1
A9: IC46.2 (E), IC47.2 (E), IC48.2 (E), IC49.2 (E), IC50.2 (E), Q10.3 (IN+), R11.1
A10: IC51.2 (E), IC52.2 (E), IC53.2 (E), IC54.2 (E), IC55.2 (E), Q11.3 (IN+), R12.1
A11: IC56.2 (E), IC57.2 (E), IC58.2 (E), IC59.2 (E), IC60.2 (E), Q12.3 (IN+), R13.1
A12: IC61.2 (E), IC62.2 (E), IC63.2 (E), IC64.2 (E), IC65.2 (E), Q13.3 (IN+), R14.1
A13: IC66.2 (E), IC67.2 (E), IC68.2 (E), IC69.2 (E), IC70.2 (E), Q14.3 (IN+), R15.1
A14: IC71.2 (E), IC72.2 (E), IC73.2 (E), IC74.2 (E), IC75.2 (E), Q15.3 (IN+), R16.1
A15: IC76.2 (E), IC77.2 (E), IC78.2 (E), IC79.2 (E), IC80.2 (E), Q16.3 (IN+), R17.1
A16: IC81.2 (E), IC82.2 (E), IC83.2 (E), IC84.2 (E), IC85.2 (E), Q17.3 (IN+), R18.1
A17: IC86.2 (E), IC87.2 (E), IC88.2 (E), IC89.2 (E), IC90.2 (E), Q18.3 (IN+), R19.1
A18: IC91.2 (E), IC92.2 (E), IC93.2 (E), IC94.2 (E), IC95.2 (E), Q19.3 (IN+), R20.1
A19: IC96.2 (E), IC97.2 (E), IC98.2 (E), IC99.2 (E), IC100.2 (E), Q20.3 (IN+), R21.1
A20: IC101.2 (E), IC102.2 (E), IC103.2 (E), IC104.2 (E), IC105.2 (E), Q21.3 (IN+), R22.1
A21: IC106.2 (E), IC107.2 (E), IC108.2 (E), IC109.2 (E), IC110.2 (E), Q22.3 (IN+), R23.1
A22: IC111.2 (E), IC112.2 (E), IC113.2 (E), IC114.2 (E), IC115.2 (E), Q23.3 (IN+), R24.1
A23: IC116.2 (E), IC117.2 (E), IC118.2 (E), IC119.2 (E), IC120.2 (E), Q24.3 (IN+), R25.1
A24: IC121.2 (E), IC122.2 (E), IC123.2 (E), IC124.2 (E), IC125.2 (E), Q25.3 (IN+), R26.1
A25: IC126.2 (E), IC127.2 (E), IC128.2 (E), IC129.2 (E), IC130.2 (E), Q26.3 (IN+), R27.1
A26: IC131.2 (E), IC132.2 (E), IC133.2 (E), IC134.2 (E), IC135.2 (E), Q27.3 (IN+), R28.1
A27: IC136.2 (E), IC137.2 (E), IC138.2 (E), IC139.2 (E), IC140.2 (E), Q28.3 (IN+), R29.1
A28: IC141.2 (E), IC142.2 (E), IC143.2 (E), IC144.2 (E), IC145.2 (E), Q29.3 (IN+), R30.1
A29: IC146.2 (E), IC147.2 (E), IC148.2 (E), IC149.2 (E), IC150.2 (E), Q30.3 (IN+), R31.1
A30: IC151.2 (E), IC152.2 (E), IC153.2 (E), IC154.2 (E), IC155.2 (E), Q31.3 (IN+), R32.1
A31: IC156.2 (E), IC157.2 (E), IC158.2 (E), IC159.2 (E), IC160.2 (E), Q32.3 (IN+), R33.1
A32: IC161.2 (E), IC162.2 (E), IC163.2 (E), IC164.2 (E), IC165.2 (E), Q33.3 (IN+), R34.1
A33: IC166.2 (E), IC167.2 (E), IC168.2 (E), IC169.2 (E), IC170.2 (E), Q34.3 (IN+), R35.1
A34: IC171.2 (E), IC172.2 (E), IC173.2 (E), IC174.2 (E), IC175.2 (E), Q35.3 (IN+), R36.1
A35: IC176.2 (E), IC177.2 (E), IC178.2 (E), IC179.2 (E), IC180.2 (E), Q36.3 (IN+), R37.1
A36: IC181.2 (E), IC182.2 (E), IC183.2 (E), IC184.2 (E), IC185.2 (E), Q37.3 (IN+), R38.1
A37: IC186.2 (E), IC187.2 (E), IC188.2 (E), IC189.2 (E), IC190.2 (E), Q38.3 (IN+), R39.1
DAC_0: Q1.1 (IN-), Q2.1 (IN-), Q3.1 (IN-), Q4.1 (IN-), Q5.1 (IN-), Q6.1 (IN-), Q7.1 (IN-), Q8.1 (IN-), Q9.1 (IN-), Q10.1 (IN-), Q11.1 (IN-), Q12.1 (IN-), Q13.1 (IN-), Q14.1 (IN-), Q15.1 (IN-), Q16.1 (IN-), Q17.1 (IN-), Q18.1 (IN-), Q19.1 (IN-), Q20.1 (IN-), Q21.1 (IN-), Q22.1 (IN-), Q23.1 (IN-), Q24.1 (IN-), Q25.1 (IN-), Q26.1 (IN-), Q27.1 (IN-), Q28.1 (IN-), Q29.1 (IN-), Q30.1 (IN-), Q31.1 (IN-), Q32.1 (IN-), Q33.1 (IN-), Q34.1 (IN-), Q35.1 (IN-), Q36.1 (IN-), Q37.1 (IN-), Q38.1 (IN-); also elsewhere on the board
GND: Q1.2 (GND), Q2.2 (GND), Q3.2 (GND), Q4.2 (GND), Q5.2 (GND), Q6.2 (GND), Q7.2 (GND), Q8.2 (GND), Q9.2 (GND), Q10.2 (GND), Q11.2 (GND), Q12.2 (GND), Q13.2 (GND), Q14.2 (GND), Q15.2 (GND), Q16.2 (GND), Q17.2 (GND), Q18.2 (GND), Q19.2 (GND), Q20.2 (GND), Q21.2 (GND), Q22.2 (GND), Q23.2 (GND), Q24.2 (GND), Q25.2 (GND), Q26.2 (GND), Q27.2 (GND), Q28.2 (GND), Q29.2 (GND), Q30.2 (GND), Q31.2 (GND), Q32.2 (GND), Q33.2 (GND), Q34.2 (GND), Q35.2 (GND), Q36.2 (GND), Q37.2 (GND), Q38.2 (GND), R2.2, R3.2, R4.2, R5.2, R6.2, R7.2, R8.2, R9.2, R10.2, R11.2, R12.2, R13.2, R14.2, R15.2, R16.2, R17.2, R18.2, R19.2, R20.2, R21.2, R22.2, R23.2, R24.2, R25.2, R26.2, R27.2, R28.2, R29.2, R30.2, R31.2, R32.2, R33.2, R34.2, R35.2, R36.2, R37.2, R38.2, R39.2; also elsewhere on the board
Line0: Q1.4 (OUTPUT); also elsewhere on the board
Line1: Q2.4 (OUTPUT); also elsewhere on the board
Line2: Q3.4 (OUTPUT); also elsewhere on the board
Line3: Q4.4 (OUTPUT); also elsewhere on the board
Line4: Q5.4 (OUTPUT); also elsewhere on the board
Line5: Q6.4 (OUTPUT); also elsewhere on the board
Line6: Q7.4 (OUTPUT); also elsewhere on the board
Line7: Q8.4 (OUTPUT); also elsewhere on the board
Line8: Q9.4 (OUTPUT); also elsewhere on the board
Line9: Q10.4 (OUTPUT); also elsewhere on the board
Line10: Q11.4 (OUTPUT); also elsewhere on the board
Line11: Q12.4 (OUTPUT); also elsewhere on the board
Line12: Q13.4 (OUTPUT); also elsewhere on the board
Line13: Q14.4 (OUTPUT); also elsewhere on the board
Line14: Q15.4 (OUTPUT); also elsewhere on the board
Line15: Q16.4 (OUTPUT); also elsewhere on the board
Line16: Q17.4 (OUTPUT); also elsewhere on the board
Line17: Q18.4 (OUTPUT); also elsewhere on the board
Line18: Q19.4 (OUTPUT); also elsewhere on the board
Line19: Q20.4 (OUTPUT); also elsewhere on the board
Line20: Q21.4 (OUTPUT); also elsewhere on the board
Line21: Q22.4 (OUTPUT); also elsewhere on the board
Line22: Q23.4 (OUTPUT); also elsewhere on the board
Line23: Q24.4 (OUTPUT); also elsewhere on the board
Line24: Q25.4 (OUTPUT); also elsewhere on the board
Line25: Q26.4 (OUTPUT); also elsewhere on the board
Line26: Q27.4 (OUTPUT); also elsewhere on the board
Line27: Q28.4 (OUTPUT); also elsewhere on the board
Line28: Q29.4 (OUTPUT); also elsewhere on the board
Line29: Q30.4 (OUTPUT); also elsewhere on the board
Line30: Q31.4 (OUTPUT); also elsewhere on the board
Line31: Q32.4 (OUTPUT); also elsewhere on the board
Line32: Q33.4 (OUTPUT); also elsewhere on the board
Line33: Q34.4 (OUTPUT); also elsewhere on the board
Line34: Q35.4 (OUTPUT); also elsewhere on the board
Line35: Q36.4 (OUTPUT); also elsewhere on the board
Line36: Q37.4 (OUTPUT); also elsewhere on the board
Line37: Q38.4 (OUTPUT); also elsewhere on the board

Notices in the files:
parts and their libraries:
Copyright 2016 Accelerated Designs. All rights reserved.
